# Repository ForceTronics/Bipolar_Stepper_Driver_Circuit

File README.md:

# Bipolar_Stepper_Driver_Circuit
Eagle files for Bipolar Stepper Motor Driver Circuit using discrete components. Go to the following YouTube page to access the tutorial https://youtu.be/apO-n8kkWQo

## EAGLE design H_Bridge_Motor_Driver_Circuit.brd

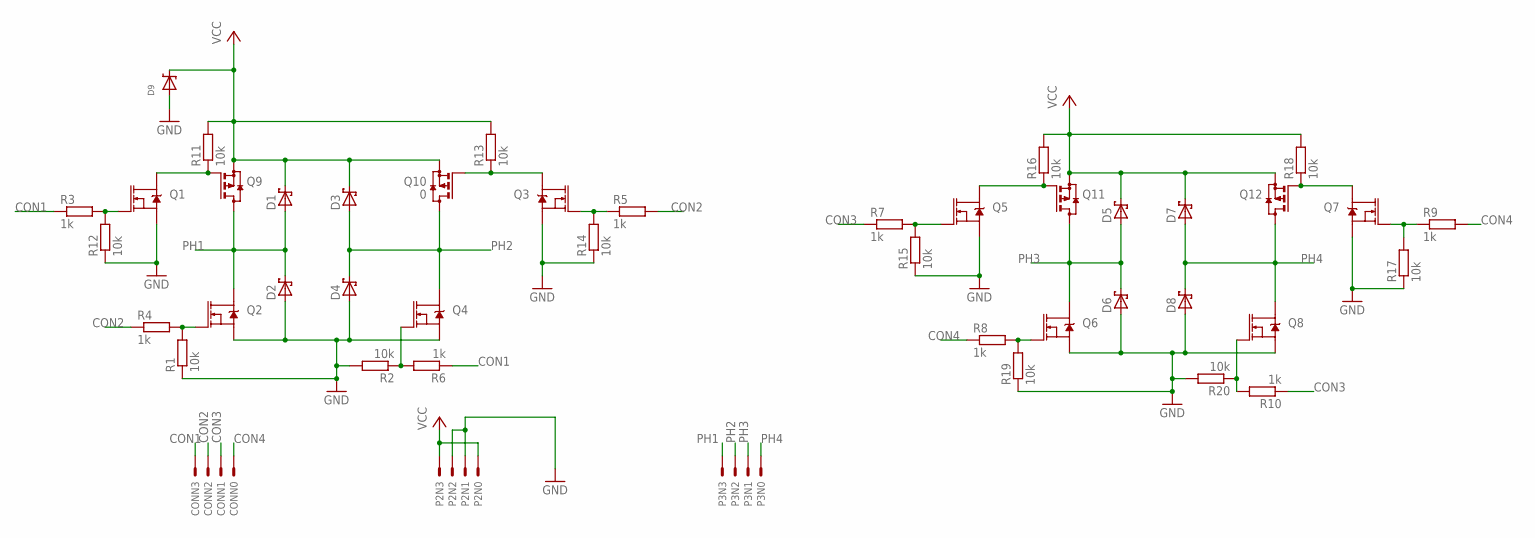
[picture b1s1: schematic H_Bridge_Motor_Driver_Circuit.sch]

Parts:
CON: 4PINHEADER
D1, D2, D3, D4, D5, D6, D7, D8: BAS40; SOT23
D9: DDZ5V6ASF
P2, P3: 4PINHEADER
Q1, Q2, Q3, Q4, Q5, Q6, Q7, Q8: MOSFET-NCH-BSS138; SOT23-3
Q9, Q11, Q12: BSS84; SOT23
Q10: 0; SOT23
R1, R2, R11, R12, R13, R14, R15, R16, R17, R18, R19, R20: 10k; R1206
R3, R4, R5, R6, R7, R8, R9, R10: 1k; R1206

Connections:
CON1: CON.N3, R3.1, R6.1
CON2: CON.N2, R4.1, R5.2
CON3: CON.N1, R7.1, R10.1
CON4: CON.N0, R8.1, R9.2
GND: D2.1 (A), D4.1 (A), D6.1 (A), D8.1 (A), D9.P$1 (A), P2.N1, P2.N2, Q1.2 (S), Q2.2 (S), Q3.2 (S), Q4.2 (S), Q5.2 (S), Q6.2 (S), Q7.2 (S), Q8.2 (S), R1.1, R2.2, R12.1, R14.1, R15.1, R17.1, R19.1, R20.2
unnamed: Q1.3 (D), Q9.1 (G), R11.1
unnamed: Q1.1 (G), R3.2, R12.2
unnamed: Q3.3 (D), Q10.1 (G), R13.1
unnamed: Q3.1 (G), R5.1, R14.2
unnamed: Q4.1 (G), R2.1, R6.2
unnamed: Q5.3 (D), Q11.1 (G), R16.1
unnamed: Q8.1 (G), R10.2, R20.1
unnamed: Q5.1 (G), R7.2, R15.2
unnamed: Q2.1 (G), R1.2, R4.2
unnamed: Q7.3 (D), Q12.1 (G), R18.1
unnamed: Q7.1 (G), R9.1, R17.2
unnamed: Q6.1 (G), R8.2, R19.2
PH1: D1.1 (A), D2.3 (C), P3.N3, Q2.3 (D), Q9.3 (D)
PH2: D3.1 (A), D4.3 (C), P3.N2, Q4.3 (D), Q10.3 (D)
PH3: D5.1 (A), D6.3 (C), P3.N1, Q6.3 (D), Q11.3 (D)
PH4: D7.1 (A), D8.3 (C), P3.N0, Q8.3 (D), Q12.3 (D)
VCC: D1.3 (C), D3.3 (C), D5.3 (C), D7.3 (C), D9.P$2 (C), P2.N0, P2.N3, Q9.2 (S), Q10.2 (S), Q11.2 (S), Q12.2 (S), R11.2, R13.2, R16.2, R18.2

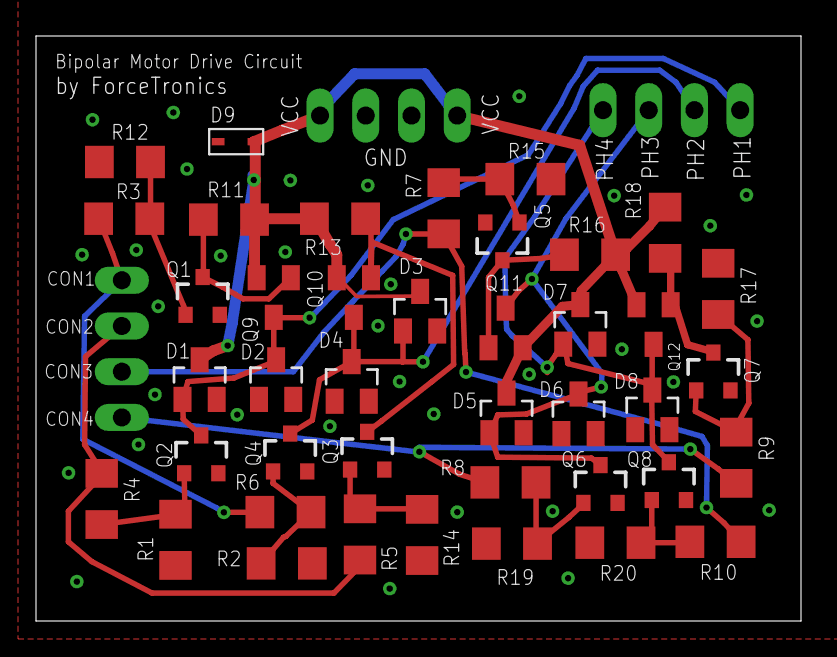
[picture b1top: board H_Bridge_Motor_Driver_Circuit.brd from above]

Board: 2 copper layers, 42.5 x 32.5 mm, 44 parts (0 on the bottom side), 22 nets.

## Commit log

2018-02-01 Create H_Bridge_Motor_Driver_Circuit.sch
    Eagle Schematic file for Bipolar Stepper Motor Driver circuit
2018-02-01 Create H_Bridge_Motor_Driver_Circuit.brd
    Eagle board file for Bipolar Stepper Motor Circuit Design

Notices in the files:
parts and their libraries:
SparkFun-DiscreteSemi: Licensing: Creative Commons ShareAlike 4.0 International - https://creativecommons.org/licenses/by-sa/4.0
